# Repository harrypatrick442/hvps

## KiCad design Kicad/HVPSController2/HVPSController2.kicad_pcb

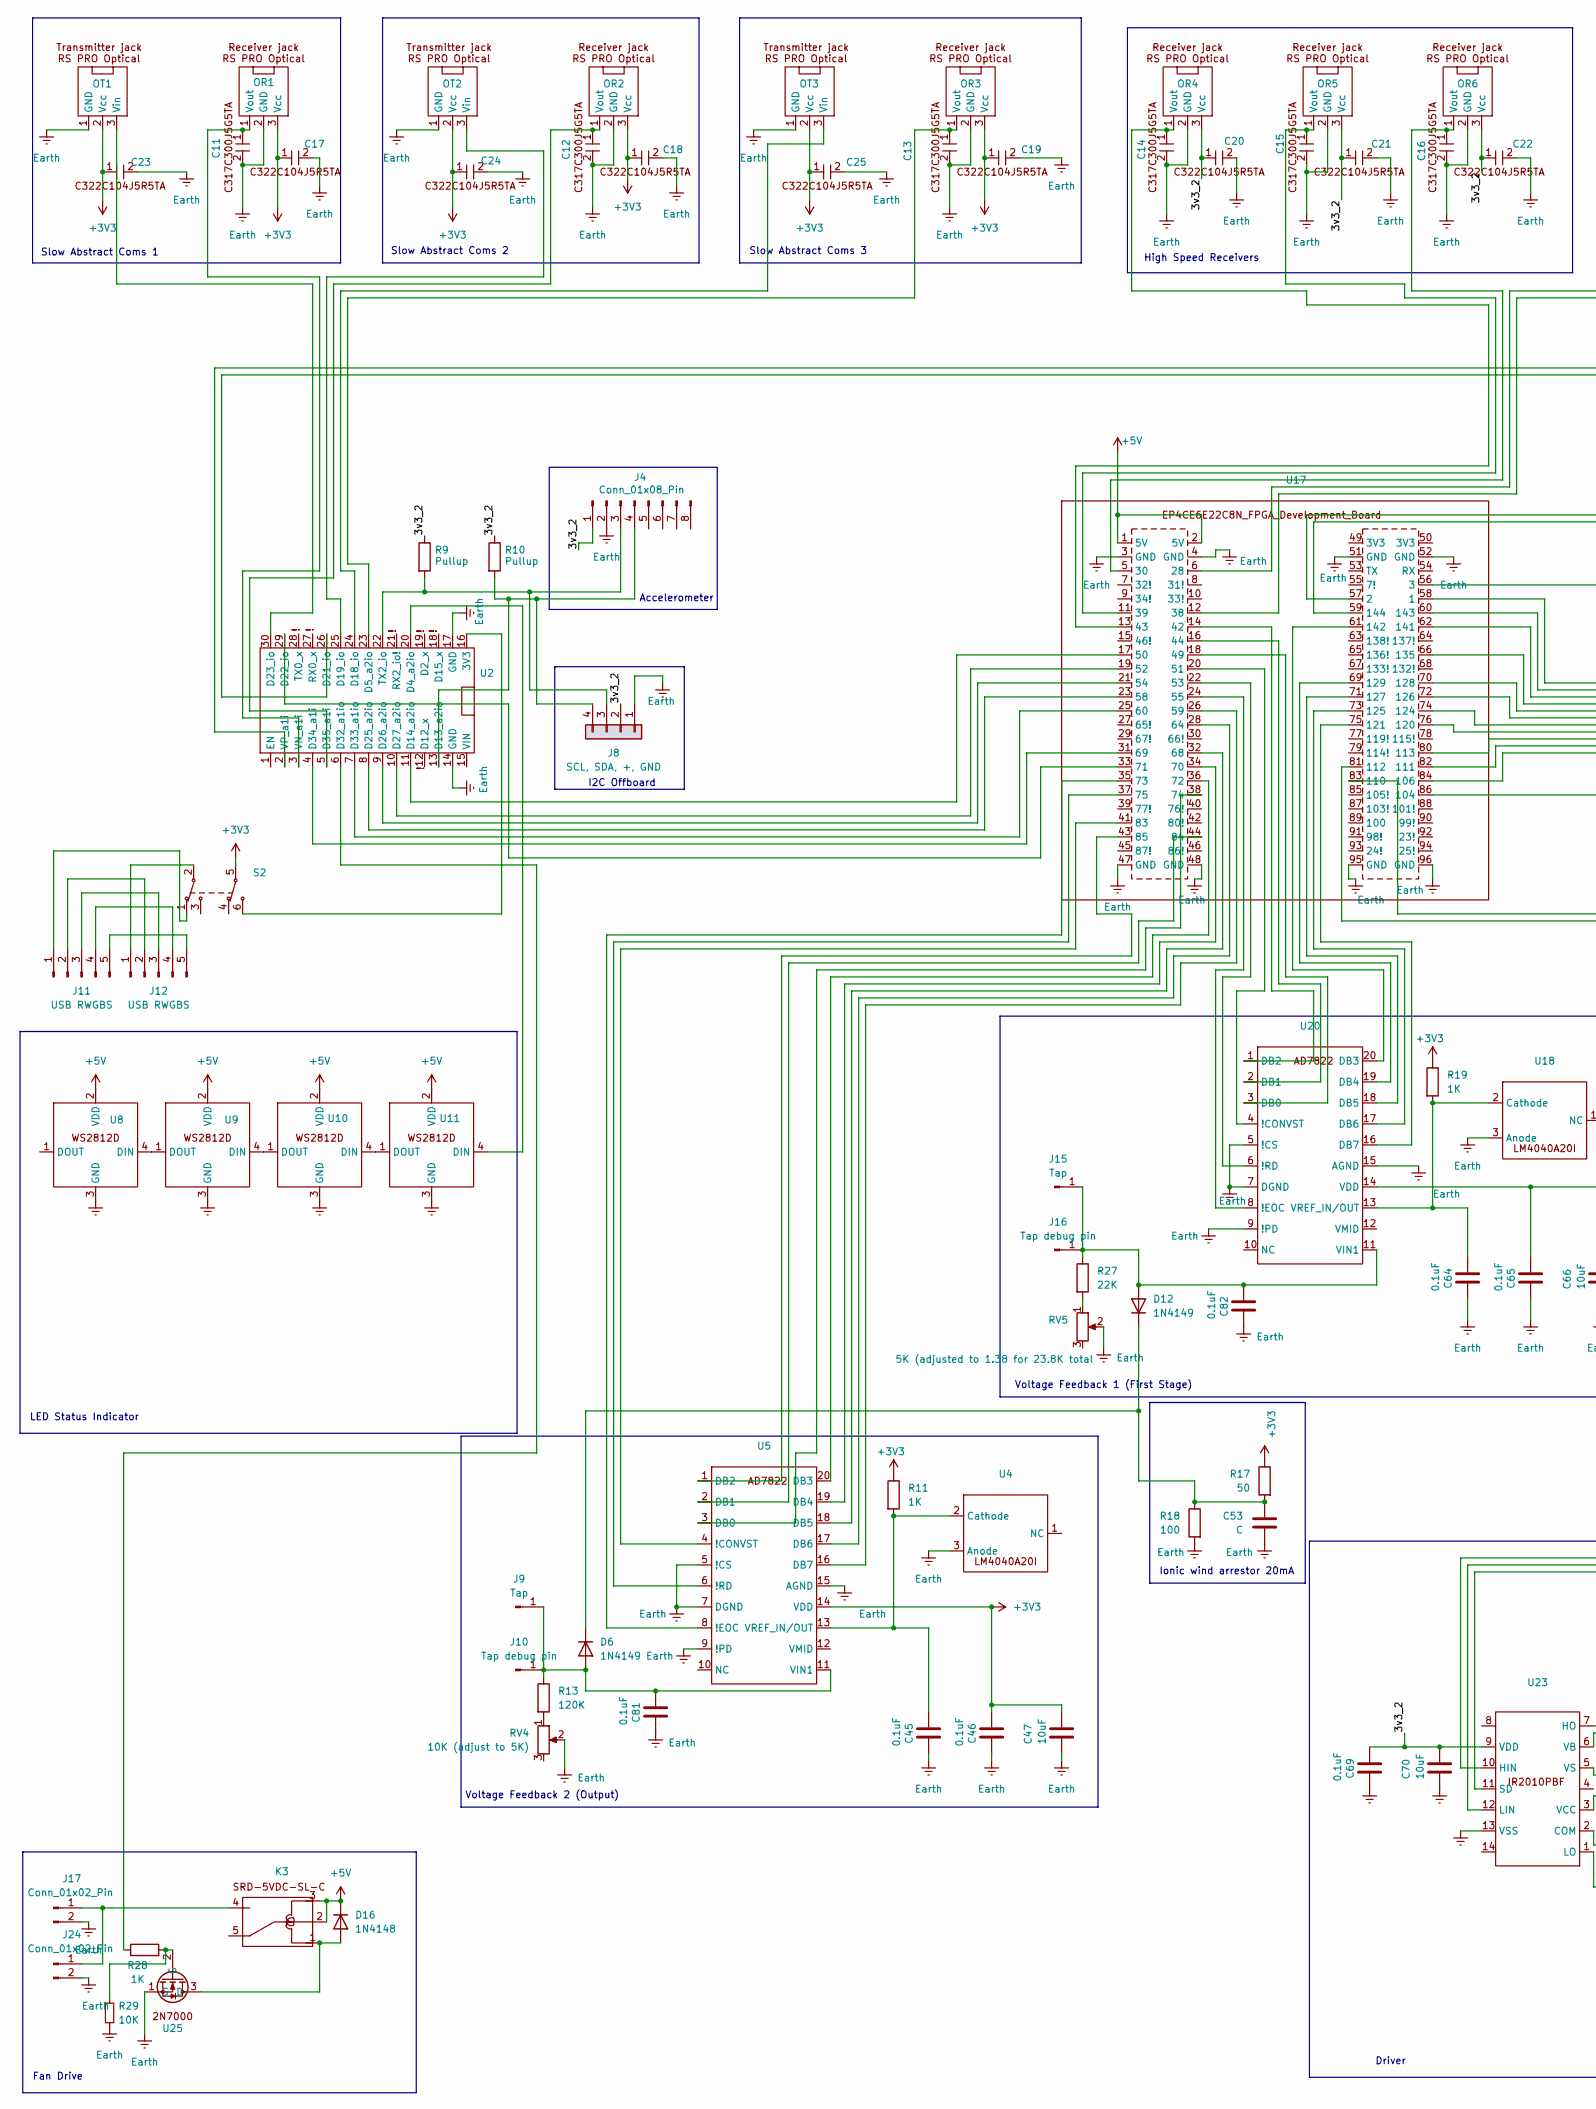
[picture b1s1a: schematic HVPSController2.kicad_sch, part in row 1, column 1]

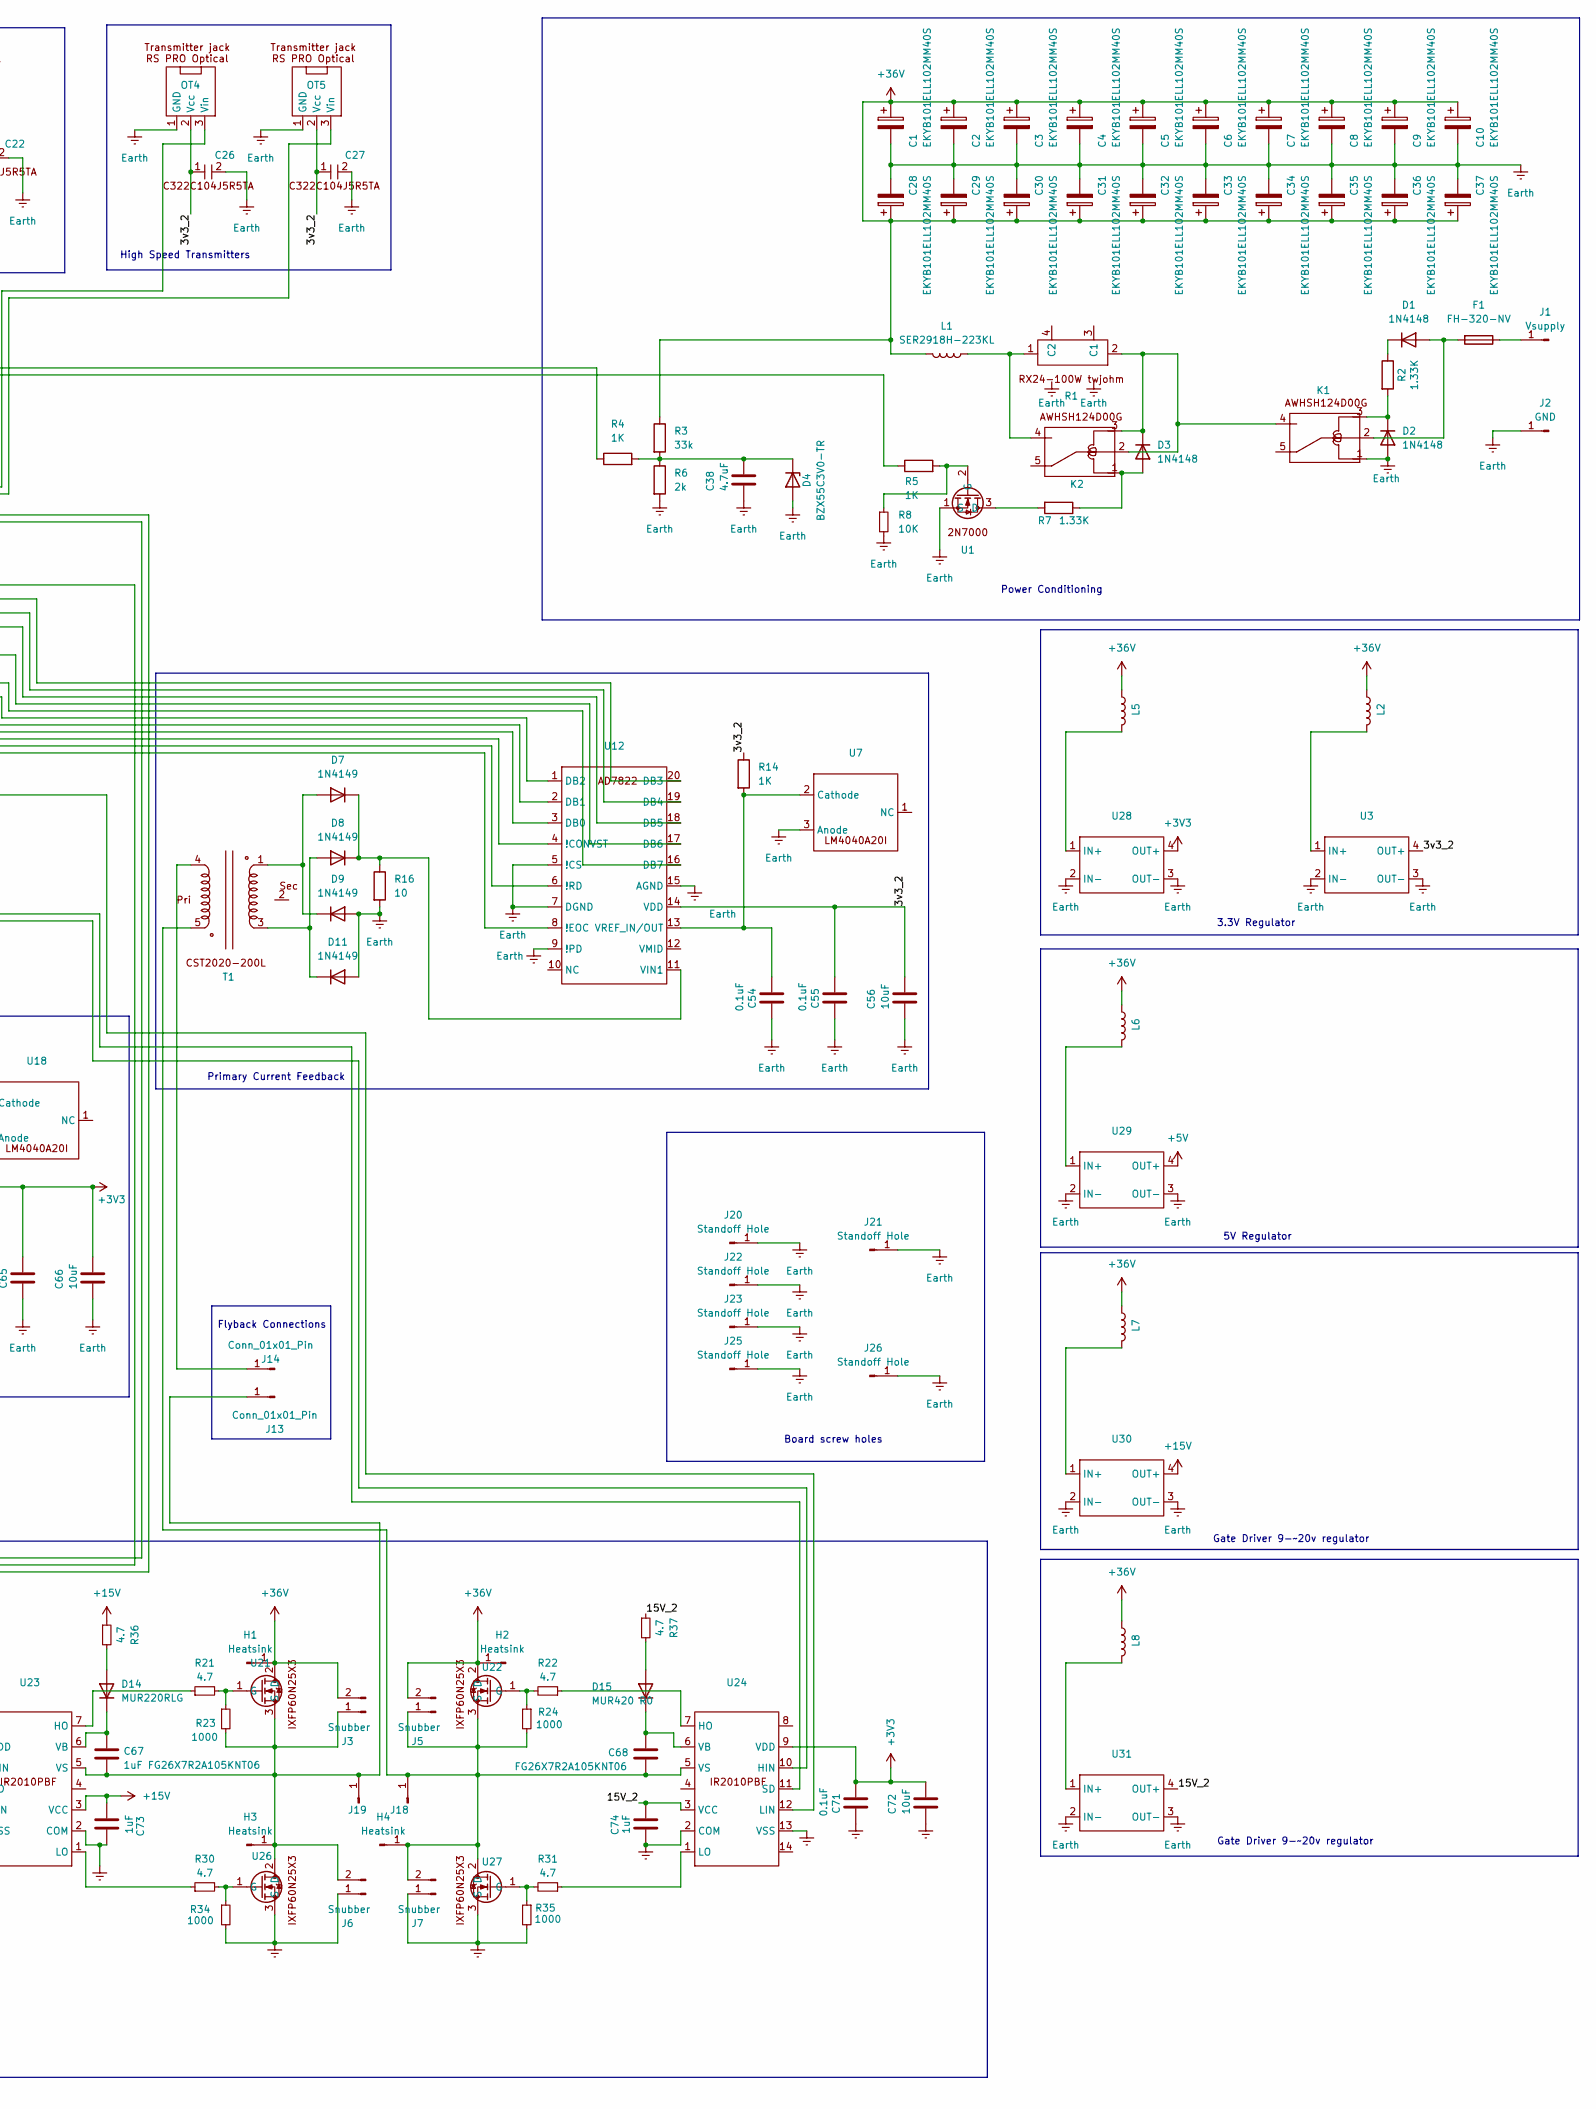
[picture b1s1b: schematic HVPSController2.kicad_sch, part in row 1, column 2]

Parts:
C1, C2, C3, C4, C5, C6, C7, C8, C9, C10, C28, C29, C30, C31, C32, C33, C34, C35, C36, C37: EKYB101ELL102MM40S
C11, C12, C13, C14, C15, C16, C17, C18, C19, C20, C21, C22, C23, C24, C25, C26, C27: C_Rect_L7.0mm_W2.5mm_P5.00mm
C38: 4.7uF; C_Rect_L7.0mm_W2.5mm_P5.00mm
C45, C46, C54, C55, C64, C65, C69, C71, C81, C82: 0.1uF; C_Rect_L7.0mm_W2.5mm_P5.00mm
C47, C56, C66, C70, C72: 10uF; C_Rect_L4.0mm_W2.5mm_P2.50mm
C53: C; C_Rect_L7.0mm_W2.5mm_P5.00mm
C67: 1uF FG26X7R2A105KNT06; C_Rect_L7.0mm_W2.0mm_P5.00mm
C68: FG26X7R2A105KNT06; C_Rect_L7.0mm_W2.0mm_P5.00mm
C73, C74: 1uF; C_Rect_L7.0mm_W2.0mm_P5.00mm
D1, D2, D3: 1N4148; D_DO-35_SOD27_P7.62mm_Horizontal
D4: BZX55C3V0-TR; D_DO-35_SOD27_P10.16mm_Horizontal
D6, D12: 1N4149; D_DO-35_SOD27_P5.08mm_Vertical_AnodeUp
D7, D8, D9, D11: 1N4149; D_DO-35_SOD27_P10.16mm_Horizontal
D14: MUR220RLG; D_DO-41_SOD81_P5.08mm_Vertical_AnodeUp
D15: MUR420 R0; D_DO-41_SOD81_P7.62mm_Horizontal
D16: 1N4148; D_DO-35_SOD27_P10.16mm_Horizontal
F1: FH-320-NV
H1, H2, H3, H4: Heatsink; 647-25ABEP
J1: Vsupply; PCB-3 (M4)
J2: GND; PCB-3 (M4)
J3, J5, J6, J7: Snubber; Snubber_Connection_1
J4: Conn_01x08_Pin; PinHeader_1x08_P2.54mm_Vertical
J8: SCL, SDA, +, GND; PinHeader_1x04_P2.54mm_Vertical
J9, J15: Tap; PCB-1 (M4)
J10, J16: Tap debug pin; PinHeader_1x01_P2.54mm_Vertical
J11, J12: USB RWGBS; USB connection
J13, J14: Conn_01x01_Pin; PCB-3 (M4)
J17, J24: Conn_01x02_Pin; JST_XH_B2B-XH-A_1x02_P2.50mm_Vertical
J18, J19: PinHeader_1x01_P2.54mm_Vertical
J20, J21, J22, J23, J25, J26: Standoff Hole; ContactViaM3
K1, K2: AWHSH124D00G
K3: SRD-5VDC-SL-C
L1: SER2918H-223KL
L2, L5, L6, L7, L8: 5026 Inductor
OR1, OR2, OR3, OR4, OR5, OR6: RS PRO Optical Receiver jack
OT1, OT2, OT3, OT4, OT5: RS Pro Optical Transmitter jack
R1: RX24-100W
R2, R7: 1.33K; R_Axial_DIN0207_L6.3mm_D2.5mm_P7.62mm_Horizontal
R3: 33k; R_Axial_DIN0207_L6.3mm_D2.5mm_P7.62mm_Horizontal
R4, R5, R11, R14, R19, R28: 1K; R_Axial_DIN0207_L6.3mm_D2.5mm_P7.62mm_Horizontal
R6: 2k; R_Axial_DIN0207_L6.3mm_D2.5mm_P7.62mm_Horizontal
R8, R29: 10K; R_Axial_DIN0207_L6.3mm_D2.5mm_P7.62mm_Horizontal
R9, R10: Pullup; R_Axial_DIN0207_L6.3mm_D2.5mm_P7.62mm_Horizontal
R13: 120K; R_Axial_DIN0207_L6.3mm_D2.5mm_P7.62mm_Horizontal
R16: 10; SL2TTED10R0F
R17: 50; R_Axial_DIN0207_L6.3mm_D2.5mm_P7.62mm_Horizontal
R18: 100; R_Axial_DIN0207_L6.3mm_D2.5mm_P7.62mm_Horizontal
R21, R30, R31: 4.7; R_Axial_DIN0207_L6.3mm_D2.5mm_P7.62mm_Horizontal
R22: 4.7; R_Axial_DIN0207_L6.3mm_D2.5mm_P10.16mm_Horizontal
R23, R34, R35: 1000; R_Axial_DIN0207_L6.3mm_D2.5mm_P7.62mm_Horizontal
R24: 1000; R_Axial_DIN0207_L6.3mm_D2.5mm_P5.08mm_Vertical
R27: 22K; R_Axial_DIN0207_L6.3mm_D2.5mm_P7.62mm_Horizontal
R36, R37: 4.7; R_Axial_DIN0207_L6.3mm_D2.5mm_P5.08mm_Vertical
RV4: 10K (adjust to 5K); Potentiometer_Bourns_3296W_Vertical
RV5: 5K (adjusted to 1.38 for 23.8K total; Potentiometer_Bourns_3296W_Vertical
S2: MSS-04A
T1: CST2020-200L
U1, U4, U7, U18, U25: TO-92
U2: ESP32_WROOM-32_Dev_Board
U3, U28, U29, U30, U31: HW-677 LM2596HVS DC-DC
U5, U12, U20: DIP-20_W7.62mm_Socket_LongPads
U8, U9, U10, U11: LED_D5.0mm-4_RGB_Wide_Pins
U17: EP4CE6E22C8N_FPGA_Development_Board_
U21, U22, U26, U27: IXFP60N25X3_2
U23, U24: DIP-14_W7.62mm_Socket_LongPads

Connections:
+5V: D16.1 (K), K3.2, K3.3, U8.2 (VDD), U9.2 (VDD), U10.2 (VDD), U11.2 (VDD), U17.1 (5V), U17.2 (5V), U29.4 (OUT+); also elsewhere on the board
+15V: C73.2, R36.1, U23.3 (VCC), U30.4 (OUT+); also elsewhere on the board
+36V: C1.1, C2.1, C3.1, C4.1, C5.1, C6.1, C7.1, C8.1, C9.1, C10.1, C28.1, C29.1, C30.1, C31.1, C32.1, C33.1, C34.1, C35.1, C36.1, C37.1, H1.1, H2.1, J3.2, J5.2, L1.2, L2.1, L5.1, L6.1, L7.1, L8.1, R3.1, U21.2 (D), U22.2 (D)
/15V_2: C74.2, R37.1, U24.3 (VCC), U31.4 (OUT+); also elsewhere on the board
unnamed: D1.2 (A), F1.2, K1.2
unnamed: D1.1 (K), R2.1
unnamed: D2.1 (K), K1.3, R2.2
unnamed: D3.2 (A), K2.1, R7.1
unnamed: D3.1 (K), K1.4, K2.2, K2.3, R1.2
unnamed: C38.1, D4.1 (K), R3.2, R4.2, R6.1
unnamed: C81.1, D6.2 (A), J9.1, J10.1, R13.1, U5.11 (VIN1)
unnamed: D7.2 (A), D9.1 (K), T1.1
unnamed 12: D7.1 (K), D8.1 (K), R16.1, U12.11 (VIN1); also elsewhere on the board
unnamed: D8.2 (A), D11.1 (K), T1.3
unnamed: C82.1, D12.2 (A), J15.1, J16.1, R27.1, U20.11 (VIN1)
unnamed: C53.1, D6.1 (K), D12.1 (K), R17.2, R18.1
unnamed: D14.2 (A), R36.2
unnamed: C67.2, D14.1 (K), U23.6 (VB)
unnamed: D15.2 (A), R37.2
unnamed: C68.2, D15.1 (K), U24.6 (VB)
unnamed: D16.2 (A), K3.1, U25.3 (D)
unnamed: C67.1, H3.1, J3.1, J6.2, J13.1, J18.1, R23.2, U21.3 (S), U23.5 (VS), U26.2 (D)
unnamed: F1.1, J1.1
unnamed: J11.1, S2.1
unnamed: J11.2, J12.2
unnamed: J11.3, J12.3
unnamed: J11.4, J12.4
unnamed: J11.5, J12.5
unnamed: J12.1, S2.2
unnamed: J14.1, T1.4
unnamed: J17.1, J24.1, K3.4
unnamed: K2.4, L1.1, R1.1
unnamed: C11.1, OR1.1 (Vout), U2.3 (VN_a1i)
unnamed: C12.1, OR2.1 (Vout), U2.5 (D35_a1i)
unnamed: C13.1, OR3.1 (Vout), U2.23 (D5_a2io)
unnamed: C14.1, OR4.1 (Vout), U17.13 (43)
unnamed: C15.1, OR5.1 (Vout), U17.11 (39)
unnamed: C16.1, OR6.1 (Vout), U17.5 (30)
unnamed: OT1.3 (Vin), U2.30 (D23_io)
unnamed: OT2.3 (Vin), U2.25 (D19_io)
unnamed: OT3.3 (Vin), U2.24 (D18_io)
unnamed: OT4.3 (Vin), U17.6 (28)
unnamed: OT5.3 (Vin), U17.12 (38)
unnamed: R13.2, RV4.1
unnamed: R27.2, RV5.1
unnamed: R7.2, U1.3 (D)
unnamed: R5.2, R8.1, U1.2 (G)
unnamed: S2.6, U2.16 (3V3)
unnamed: R5.1, U2.26 (D21_io)
unnamed: R28.1, U2.6 (D32_a1io)
unnamed: R4.1, U2.2 (VP_a1i)
unnamed: L2.2, U3.1 (IN+)
unnamed: C45.1, R11.2, U4.2 (Cathode), U5.13 (VREF_IN/OUT)
unnamed: U8.4 (DIN), U9.1 (DOUT)
unnamed: U10.4 (DIN), U11.1 (DOUT)
unnamed: U9.4 (DIN), U10.1 (DOUT)
unnamed: U2.20 (D4_a2io), U11.4 (DIN)
unnamed: U12.4 (!CONVST), U17.80 (113)
unnamed: U12.8 (!EOC), U17.84 (106)
unnamed: U12.6 (!RD), U17.82 (111)
unnamed: U12.3 (DB0), U17.76 (120)
unnamed: U12.2 (DB1), U17.74 (124)
unnamed: U12.1 (DB2), U17.72 (126)
unnamed: U12.20 (DB3), U17.58 (1)
unnamed: U12.19 (DB4), U17.60 (143)
unnamed: U12.18 (DB5), U17.62 (141)
unnamed: U12.17 (DB6), U17.66 (135)
unnamed: U12.16 (DB7), U17.70 (128)
unnamed: C54.1, R14.2, U7.2 (Cathode), U12.13 (VREF_IN/OUT)
unnamed: U17.57 (2), U23.11 (SD)
unnamed: U17.56 (3), U23.12 (LIN)
unnamed: U17.14 (42), U20.1 (DB2)
unnamed: U17.16 (44), U20.2 (DB1)
unnamed: U17.18 (49), U20.3 (DB0)
unnamed: U2.11 (D14_a2io), U17.17 (50)
unnamed: U17.20 (51), U20.4 (!CONVST)
unnamed: U2.10 (D27_a2io), U17.19 (52)
unnamed: U17.22 (53), U20.6 (!RD)
unnamed: U2.9 (D26_a2io), U17.21 (54)
unnamed: U17.24 (55), U20.8 (!EOC)
unnamed: U2.8 (D25_a2io), U17.23 (58)
unnamed: U5.16 (DB7), U17.26 (59)
unnamed: U2.7 (D33_a1io), U17.25 (60)
unnamed: U5.17 (DB6), U17.28 (64)
unnamed: U5.18 (DB5), U17.32 (68)
unnamed: U2.4 (D34_a1i), U17.31 (69)
unnamed: U5.19 (DB4), U17.34 (70)
unnamed: U2.29 (D22_io), U17.33 (71)
unnamed: U5.20 (DB3), U17.36 (72)
unnamed: U5.8 (!EOC), U17.35 (73)
unnamed: U5.3 (DB0), U17.38 (74)
unnamed: U5.6 (!RD), U17.37 (75)
unnamed: U5.4 (!CONVST), U17.41 (83)
unnamed: U5.2 (DB1), U17.44 (84)
unnamed: U5.1 (DB2), U17.43 (85)
unnamed: U17.86 (104), U24.12 (LIN)
unnamed: U17.83 (110), U24.11 (SD)
unnamed: U17.81 (112), U24.10 (HIN)
unnamed: U17.75 (121), U20.16 (DB7)
unnamed: U17.73 (125), U20.17 (DB6)
unnamed: U17.71 (127), U20.18 (DB5)
unnamed: U17.69 (129), U20.19 (DB4)
unnamed: U17.61 (142), U20.20 (DB3)
unnamed: U17.59 (144), U23.10 (HIN)
unnamed: C64.1, R19.2, U18.2 (Cathode), U20.13 (VREF_IN/OUT)
unnamed: R21.2, R23.1, U21.1 (G)
unnamed: R21.1, U23.7 (HO)
unnamed: R30.1, U23.1 (LO)
unnamed: R22.1, U24.7 (HO)
unnamed: R31.1, U24.1 (LO)
unnamed: R28.2, R29.1, U25.2 (G)
unnamed: R30.2, R34.1, U26.1 (G)
unnamed: R31.2, R35.1, U27.1 (G)
unnamed: L5.2, U28.1 (IN+)
unnamed: L6.2, U29.1 (IN+)
unnamed: L7.2, U30.1 (IN+)
unnamed: L8.2, U31.1 (IN+)

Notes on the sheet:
High Speed Transmitters
Slow Abstract Coms 3
Voltage Feedback 1 (First Stage)
Driver
Primary Current Feedback
High Speed Receivers
Flyback Connections
Ionic wind arrestor 20mA
Gate Driver 9-~20v regulator
Fan Drive
LED Status Indicator
Voltage Feedback 2 (Output)
Slow Abstract Coms 2
3.3V Regulator
Board screw holes
Power Conditioning
I2C Offboard
5V Regulator
Accelerometer
Slow Abstract Coms 1

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
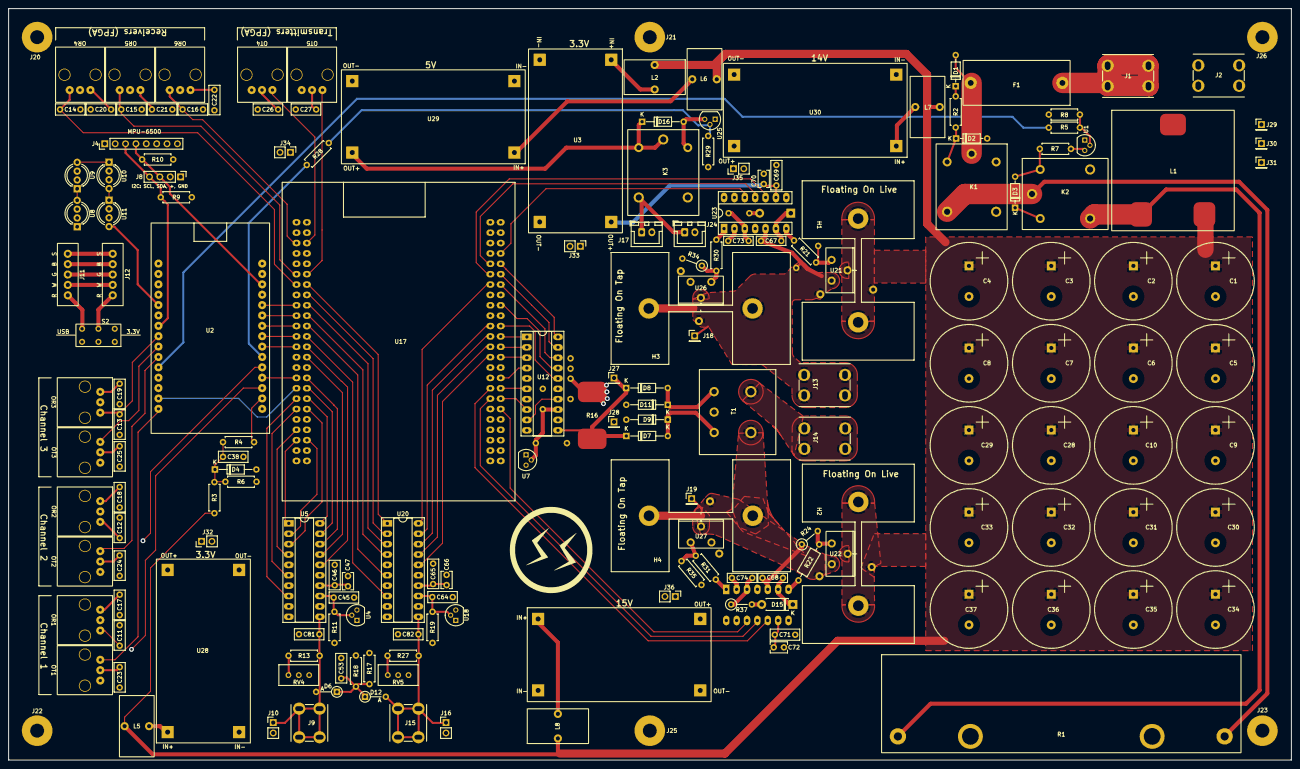
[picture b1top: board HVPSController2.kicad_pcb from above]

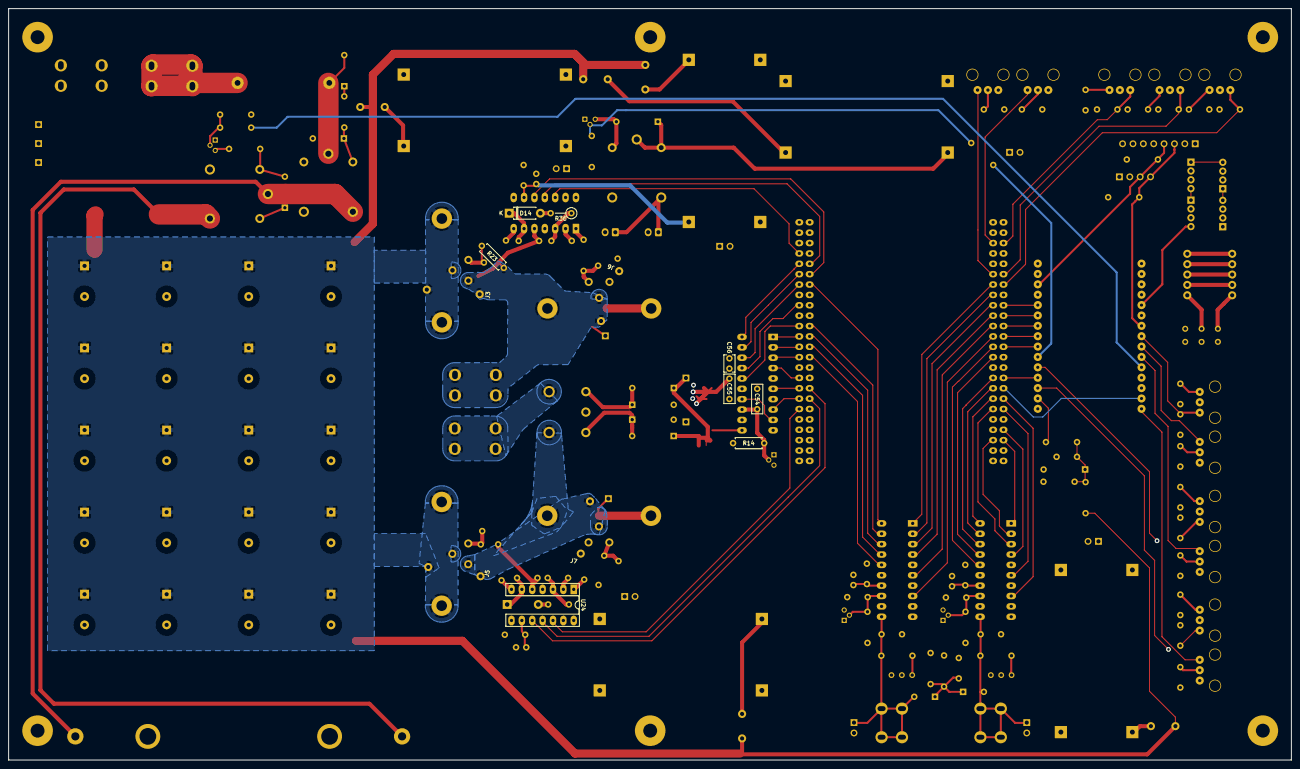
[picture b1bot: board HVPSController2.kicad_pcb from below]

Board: 4 copper layers, 314.1 x 184.0 mm, 191 parts (12 on the bottom side), 124 nets.

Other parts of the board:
J27, J28, J29, J30, J31: PinHeader_1x01_P2.54mm_Vertical
J32, J33, J34, J35, J36: Conn_01x02_Pin; PinHeader_1x02_P2.54mm_Vertical

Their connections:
+5V: J34.1; also elsewhere on the board
+15V: J35.1; also elsewhere on the board
/15V_2: J36.1; also elsewhere on the board
unnamed 12: J27.1; also elsewhere on the board

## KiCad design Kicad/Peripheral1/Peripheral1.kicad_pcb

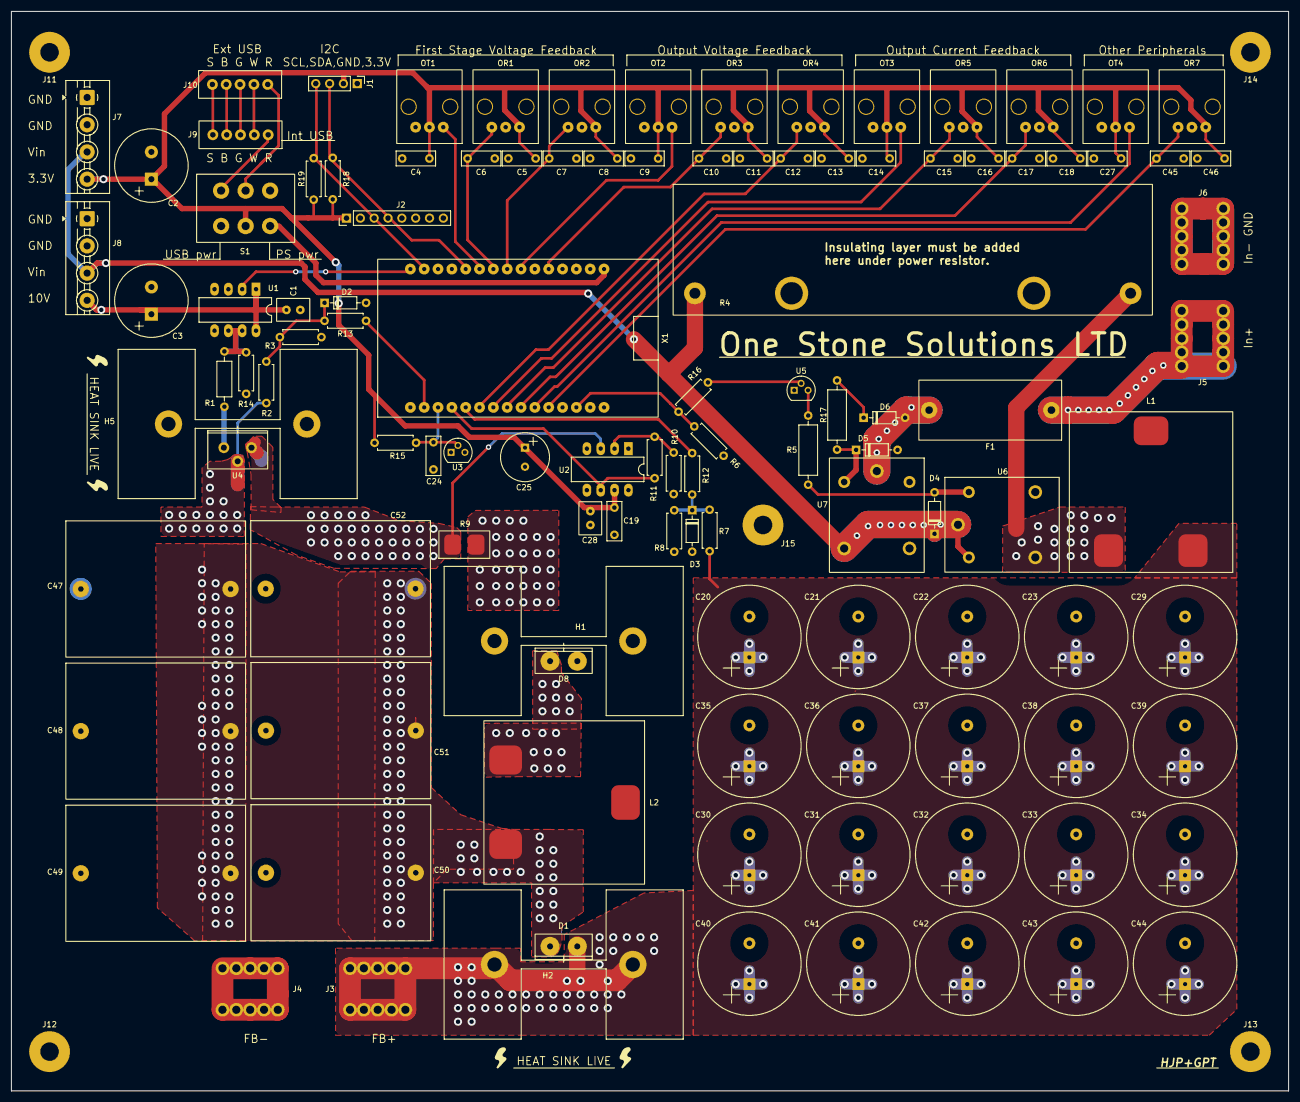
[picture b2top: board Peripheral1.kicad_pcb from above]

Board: 2 copper layers, 234.5 x 198.2 mm, 118 parts (0 on the bottom side), 48 nets.

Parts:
C1: C_drive 1uF; C320C105K5R5TA
C2, C3: 1000uF UPW1E102MHD; UPW1E102MHD
C4, C5, C6, C7, C8, C9, C10, C11, C12, C13, C14, C15, C16, C17, C18, C27, C45, C46: C_Rect_L7.0mm_W2.5mm_P5.00mm
C19: 0.1uF within 2mm; C_Disc_D7.0mm_W2.5mm_P5.00mm
C20, C21, C22, C23, C29, C30, C31, C32, C33, C34, C35, C36, C37, C38, C39, C40, C41, C42, C43, C44: EKYB101ELL102MM40S
C24: 0.1uF low ESR Ceramic; C_Rect_L7.0mm_W2.5mm_P5.00mm
C25: 100uF UHD1H101MPD1TD; UHD1H101MPD1TD
C28: 1uF; C320C105K5R5TA
C47, C48, C49, C50, C51, C52: R75RR322050L4J
D1, D8: MBR40250G
D2, D3: D_DO-35_SOD27_P7.62mm_Horizontal
D4, D5, D6: 1N4148; D_DO-35_SOD27_P7.62mm_Horizontal
F1: FH-320-NV
H1: Heatsink 1; 647-25ABEP
H2: Heatsink 2; 647-25ABEP
H5: Heatsink 5; 647-25ABEP
J1: SCL, SDA, +, GND; PinHeader_1x04_P2.54mm_Vertical
J2: Conn_01x08_Pin; PinHeader_1x08_P2.54mm_Vertical
J3, J4: Conn_01x01_Pin; 5055556-9
J5: +36V; 5055556-9
J6: GND; 5055556-9
J7, J8: Conn_01x04_Pin; TerminalBlock_MaiXu_MX126-5.0-04P_1x04_P5.00mm
J9, J10: USB RWGBS; USB connection
J11, J12, J13, J14, J15: Standoff Hole; ContactViaM3
L1: SER2918H-223KL
L2: 74436411500
OR1, OR2, OR3, OR4, OR5, OR6, OR7: RS PRO Optical Receiver jack
OT1, OT2, OT3, OT4: RS Pro Optical Transmitter jack
R1: R_drive 5; R_Axial_DIN0207_L6.3mm_D2.5mm_P10.16mm_Horizontal
R2: R_sfb_H 500K; R_Axial_DIN0207_L6.3mm_D2.5mm_P7.62mm_Horizontal
R3: R_sfb_L 6.8K; R_Axial_DIN0207_L6.3mm_D2.5mm_P7.62mm_Horizontal
R4: RX24-100W
R5, R17: 1.33K; R_Axial_DIN0309_L9.0mm_D3.2mm_P12.70mm_Horizontal
R6: 10K; R_Axial_DIN0207_L6.3mm_D2.5mm_P7.62mm_Horizontal
R7: R_pfb_H 270K; R_Axial_DIN0207_L6.3mm_D2.5mm_P7.62mm_Horizontal
R8: R_pfb_ 10K; R_Axial_DIN0207_L6.3mm_D2.5mm_P7.62mm_Horizontal
R9: R_pcfb_sense 0.001; PCS2512FR0010ET
R10: R_pcfb_in 1K; R_Axial_DIN0207_L6.3mm_D2.5mm_P7.62mm_Horizontal
R11: R_pcfb_f 56K; R_Axial_DIN0207_L6.3mm_D2.5mm_P7.62mm_Horizontal
R12: R_pfb_i 1K; R_Axial_DIN0207_L6.3mm_D2.5mm_P7.62mm_Horizontal
R13: R_sfb_i 1K; R_Axial_DIN0207_L6.3mm_D2.5mm_P7.62mm_Horizontal
R14: R_pulldown 1000; R_Axial_DIN0207_L6.3mm_D2.5mm_P7.62mm_Horizontal
R15: 3K; R_Axial_DIN0207_L6.3mm_D2.5mm_P7.62mm_Horizontal
R16: 1K; R_Axial_DIN0207_L6.3mm_D2.5mm_P7.62mm_Horizontal
R18, R19: Pullup; R_Axial_DIN0207_L6.3mm_D2.5mm_P7.62mm_Horizontal
S1: SLW-1678105-6A-N-D
U1, U2: CERDIP-8_W7.62mm_SideBrazed_LongPads
U3, U5: TO-92
U4: IXFP60N25X3
U6, U7: AWHSH124D00G
X1: ESP32_WROOM-32_Dev_Board

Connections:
+3V3: C2.1, C4.1, C5.1, C8.1, C9.1, C11.1, C13.1, C14.1, C16.1, C18.1, C19.1, C25.1, C27.1, C28.1, C46.1, J1.2, J2.1, J7.4, OR1.3 (Vcc), OR2.3 (Vcc), OR3.3 (Vcc), OR4.3 (Vcc), OR5.3 (Vcc), OR6.3 (Vcc), OR7.3 (Vcc), OT1.2 (Vcc), OT2.2 (Vcc), OT3.2 (Vcc), OT4.2 (Vcc), R15.1, R18.1, R19.1, S1.5, U2.7 (VDD)
+10V: C1.2, C3.1, J8.4, U1.1 (VDD), U1.8 (VDD)
Earth: C1.1, C2.2, C3.2, C4.2, C5.2, C6.2, C7.2, C8.2, C9.2, C10.2, C11.2, C12.2, C13.2, C14.2, C15.2, C16.2, C17.2, C18.2, C19.2, C20.2, C21.2, C22.2, C23.2, C24.2, C25.2, C27.2, C28.2, C29.2, C30.2, C31.2, C32.2, C33.2, C34.2, C35.2, C36.2, C37.2, C38.2, C39.2, C40.2, C41.2, C42.2, C43.2, C44.2, C45.2, C46.2, D2.2, D3.2, D5.2 (A), D8.2 (A), H1.1, H5.1, J1.1, J2.2, J6.1, J7.1, J7.2, J8.1, J8.2, J11.1, J12.1, J13.1, J14.1, J15.1, OR1.2 (GND), OR2.2 (GND), OR3.2 (GND), OR4.2 (GND), OR5.2 (GND), OR6.2 (GND), OR7.2 (GND), OT1.1 (GND), OT2.1 (GND), OT3.1 (GND), OT4.1 (GND), R3.2, R4.3 (C1), R4.4 (C2), R6.2, R8.2, R9.2, R10.2, R14.2, U1.4 (GND), U1.5 (GND), U2.4 (VSS), U3.3 (Anode), U5.1 (S), U7.1, X1.14 (GND), X1.17 (GND)
unnamed: C47.1, C48.1, C49.1, C50.1, C51.1, C52.1, D1.2 (A), L2.2
unnamed: C20.1, C21.1, C22.1, C23.1, C29.1, C30.1, C31.1, C32.1, C33.1, C34.1, C35.1, C36.1, C37.1, C38.1, C39.1, C40.1, C41.1, C42.1, C43.1, C44.1, D1.1 (K), H2.1, J3.1, L1.2, R7.1
unnamed: D2.1, R2.2, R3.1, R13.2
unnamed: D3.1, R7.2, R8.1, R12.2
unnamed: D4.2 (A), R5.1, U6.1
unnamed: D4.1 (K), J7.3, J8.3, R4.1, U6.2, U6.3, U7.4
unnamed: D5.1 (K), R17.2, U7.3
unnamed: D6.2 (A), F1.2, U7.2
unnamed: D6.1 (K), R17.1
unnamed: D8.1 (K), L2.1
unnamed: J1.3, J2.4, R18.2, X1.26 (D21_io)
unnamed: J1.4, J2.3, R19.2, X1.29 (D22_io)
unnamed: C47.2, C48.2, C49.2, C50.2, C51.2, C52.2, J4.1, R2.1, U4.2 (D)
unnamed: F1.1, J5.1
unnamed: J9.1, S1.1
unnamed: J10.1, S1.2
unnamed: J9.2, J10.2
unnamed: J9.3, J10.3
unnamed: J9.4, J10.4
unnamed: J9.5, J10.5
unnamed: L1.1, R4.2, U6.4
unnamed: C6.1, OR1.1 (Vout), X1.24 (D18_io)
unnamed: C7.1, OR2.1 (Vout), X1.23 (D5_a2io)
unnamed: C10.1, OR3.1 (Vout), X1.20 (D4_a2io)
unnamed: C12.1, OR4.1 (Vout), X1.6 (D32_a1io)
unnamed: C15.1, OR5.1 (Vout), X1.8 (D25_a2io)
unnamed: C17.1, OR6.1 (Vout), X1.9 (D26_a2io)
unnamed: C45.1, OR7.1 (Vout), X1.11 (D14_a2io)
unnamed: OT1.3 (Vin), X1.25 (D19_io)
unnamed: OT2.3 (Vin), X1.22 (TX2_io)
unnamed: OT3.3 (Vin), X1.7 (D33_a1io)
unnamed: OT4.3 (Vin), X1.10 (D27_a2io)
unnamed: R1.1, R14.1, U1.6 (OUT), U1.7 (OUT)
unnamed: U1.2 (IN), X1.30 (D23_io)
unnamed: R9.1, U2.3 (VIN+), U4.3 (S)
unnamed: R10.1, R11.2, U2.2 (VIN-)
unnamed: R11.1, U2.6 (VOUT), X1.4 (D34_a1i)
unnamed: C24.1, R15.2, U3.2 (Cathode), X1.3 (VN_a1i)
unnamed: R1.2, U4.1 (G)
unnamed: R5.2, U5.3 (D)
unnamed: R16.2, U5.2 (G)
unnamed: S1.6, X1.16 (3V3)
unnamed: R6.1, R16.1, X1.13 (D13_a2io)
unnamed: R12.1, X1.5 (D35_a1i)
unnamed: R13.1, X1.2 (VP_a1i)

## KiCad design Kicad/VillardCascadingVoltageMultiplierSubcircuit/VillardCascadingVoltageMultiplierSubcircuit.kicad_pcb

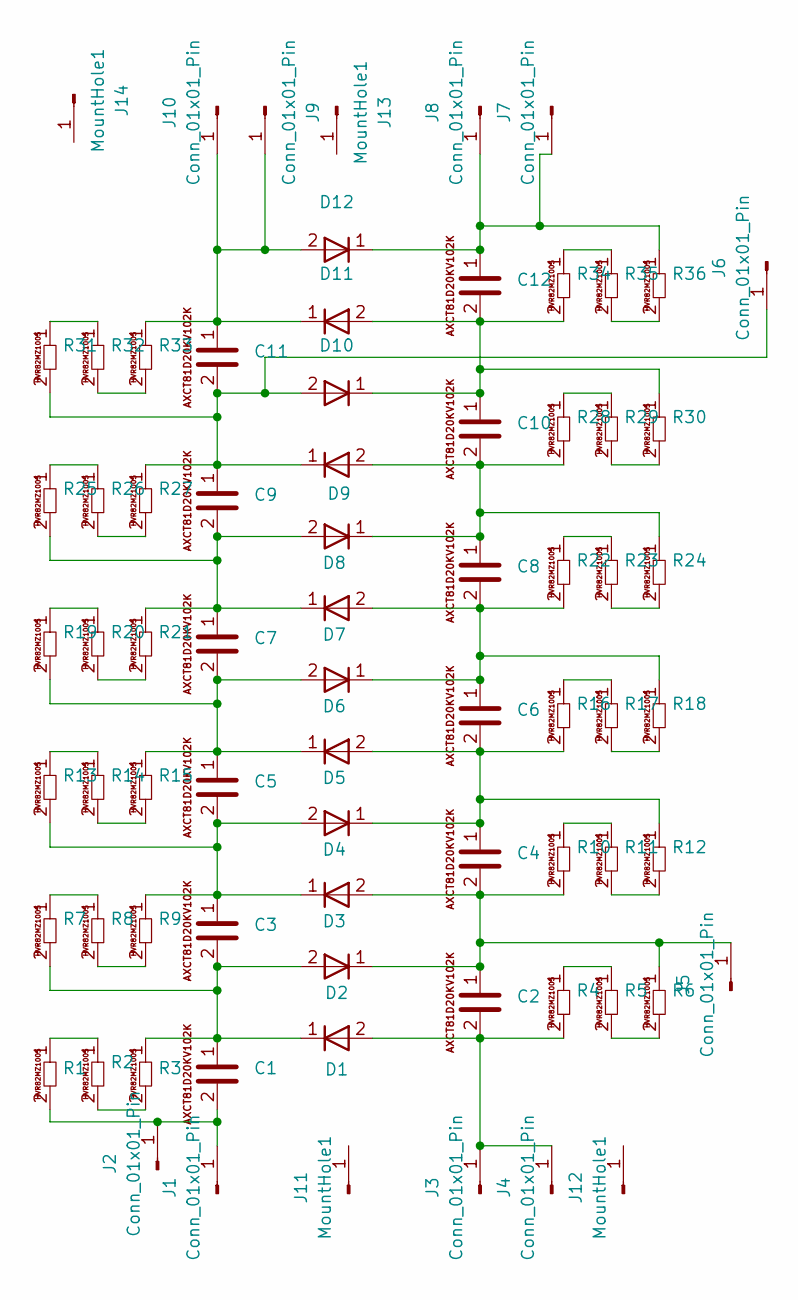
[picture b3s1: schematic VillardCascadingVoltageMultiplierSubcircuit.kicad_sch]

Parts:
C1, C2, C3, C4, C5, C6, C7, C8, C9, C10, C11, C12: AXCT81D20KV102K
D1, D2, D3, D4, D5, D6, D7, D8, D9, D10, D11, D12: 2CL2FR_JB289_MT100F35
J1, J2, J3, J4, J5, J6, J7, J8, J9, J10: Conn_01x01_Pin; VersatilePad
J11, J12, J13, J14: MountHole1; M3Hole
R1, R2, R3, R4, R5, R6, R7, R8, R9, R10, R11, R12, R13, R14, R15, R16, R17, R18, R19, R20, R21, R22, R23, R24, R25, R26, R27, R28, R29, R30, R31, R32, R33, R34, R35, R36: HVR82MZ1005

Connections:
unnamed: C1.1, C3.2, D1.1, D2.2, R3.1, R7.2
unnamed: C3.1, C5.2, D3.1, D4.2, R9.1, R13.2
unnamed: C4.1, C6.2, D4.1, D5.2, R12.1, R16.2
unnamed: C5.1, C7.2, D5.1, D6.2, R15.1, R19.2
unnamed: C6.1, C8.2, D6.1, D7.2, R18.1, R22.2
unnamed: C7.1, C9.2, D7.1, D8.2, R21.1, R25.2
unnamed: C10.1, C12.2, D10.1, D11.2, R30.1, R34.2
unnamed: C8.1, C10.2, D8.1, D9.2, R24.1, R28.2
unnamed: C1.2, J1.1, J2.1, R1.2
unnamed: C2.2, D1.2, J3.1, J4.1, R4.2
unnamed: C2.1, C4.2, D2.1, D3.2, J5.1, R6.1, R10.2
unnamed: C9.1, C11.2, D9.1, D10.2, J6.1, R27.1, R31.2
unnamed: C12.1, D12.1, J7.1, J8.1, R36.1
unnamed: C11.1, D11.1, D12.2, J9.1, J10.1, R33.1
unnamed: R1.1, R2.1
unnamed: R2.2, R3.2
unnamed: R4.1, R5.1
unnamed: R5.2, R6.2
unnamed: R7.1, R8.1
unnamed: R8.2, R9.2
unnamed: R10.1, R11.1
unnamed: R11.2, R12.2
unnamed: R13.1, R14.1
unnamed: R14.2, R15.2
unnamed: R16.1, R17.1
unnamed: R17.2, R18.2
unnamed: R19.1, R20.1
unnamed: R20.2, R21.2
unnamed: R22.1, R23.1
unnamed: R23.2, R24.2
unnamed: R25.1, R26.1
unnamed: R26.2, R27.2
unnamed: R28.1, R29.1
unnamed: R29.2, R30.2
unnamed: R31.1, R32.1
unnamed: R32.2, R33.2
unnamed: R34.1, R35.1
unnamed: R35.2, R36.2

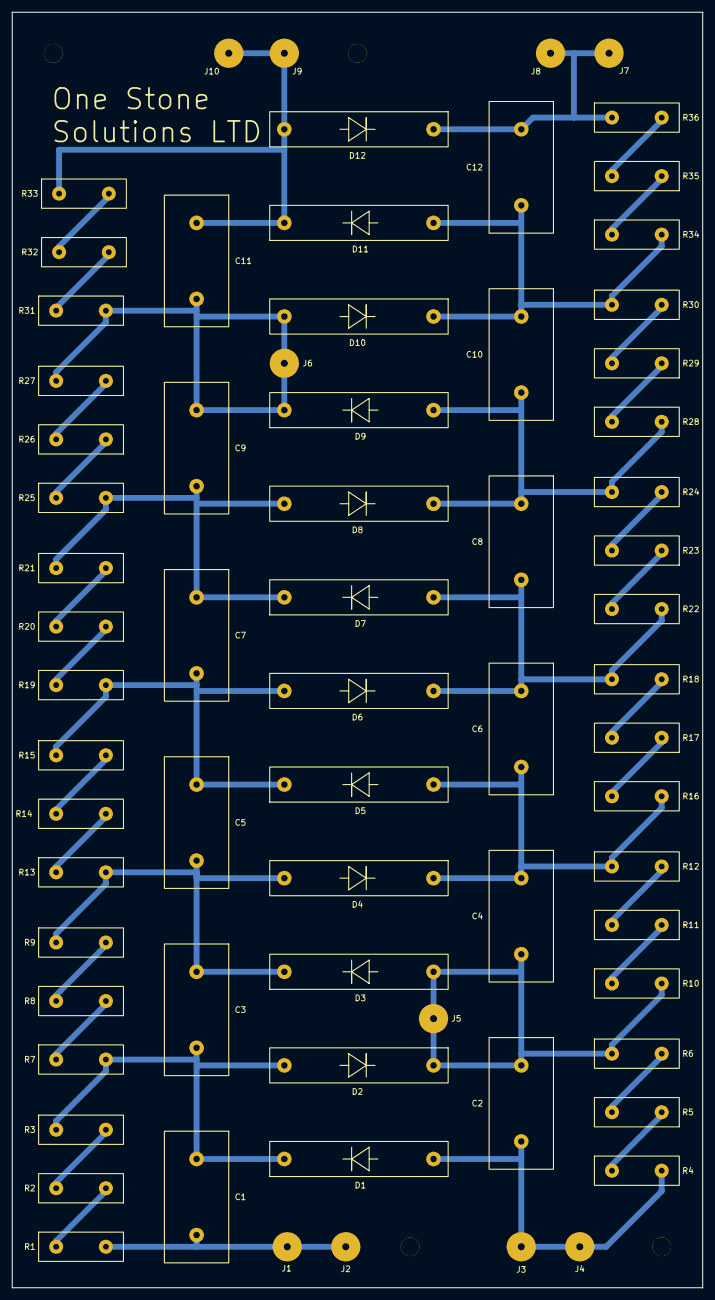
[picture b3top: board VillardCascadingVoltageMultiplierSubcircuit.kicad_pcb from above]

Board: 2 copper layers, 118.0 x 218.0 mm, 74 parts (0 on the bottom side), 38 nets.
